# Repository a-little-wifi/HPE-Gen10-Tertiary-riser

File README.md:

# HPE DL360/DL380 Gen10 Tertiary riser reverse engineering

KiCad project of an almost-complete recreation of the 875539-001 riser for the DL360 Gen10 which plugs into the tertiary riser slot on the motherboard.  
My goal is to recreate the tertiary riser for the DL380 Gen10, which should use the same pinout.

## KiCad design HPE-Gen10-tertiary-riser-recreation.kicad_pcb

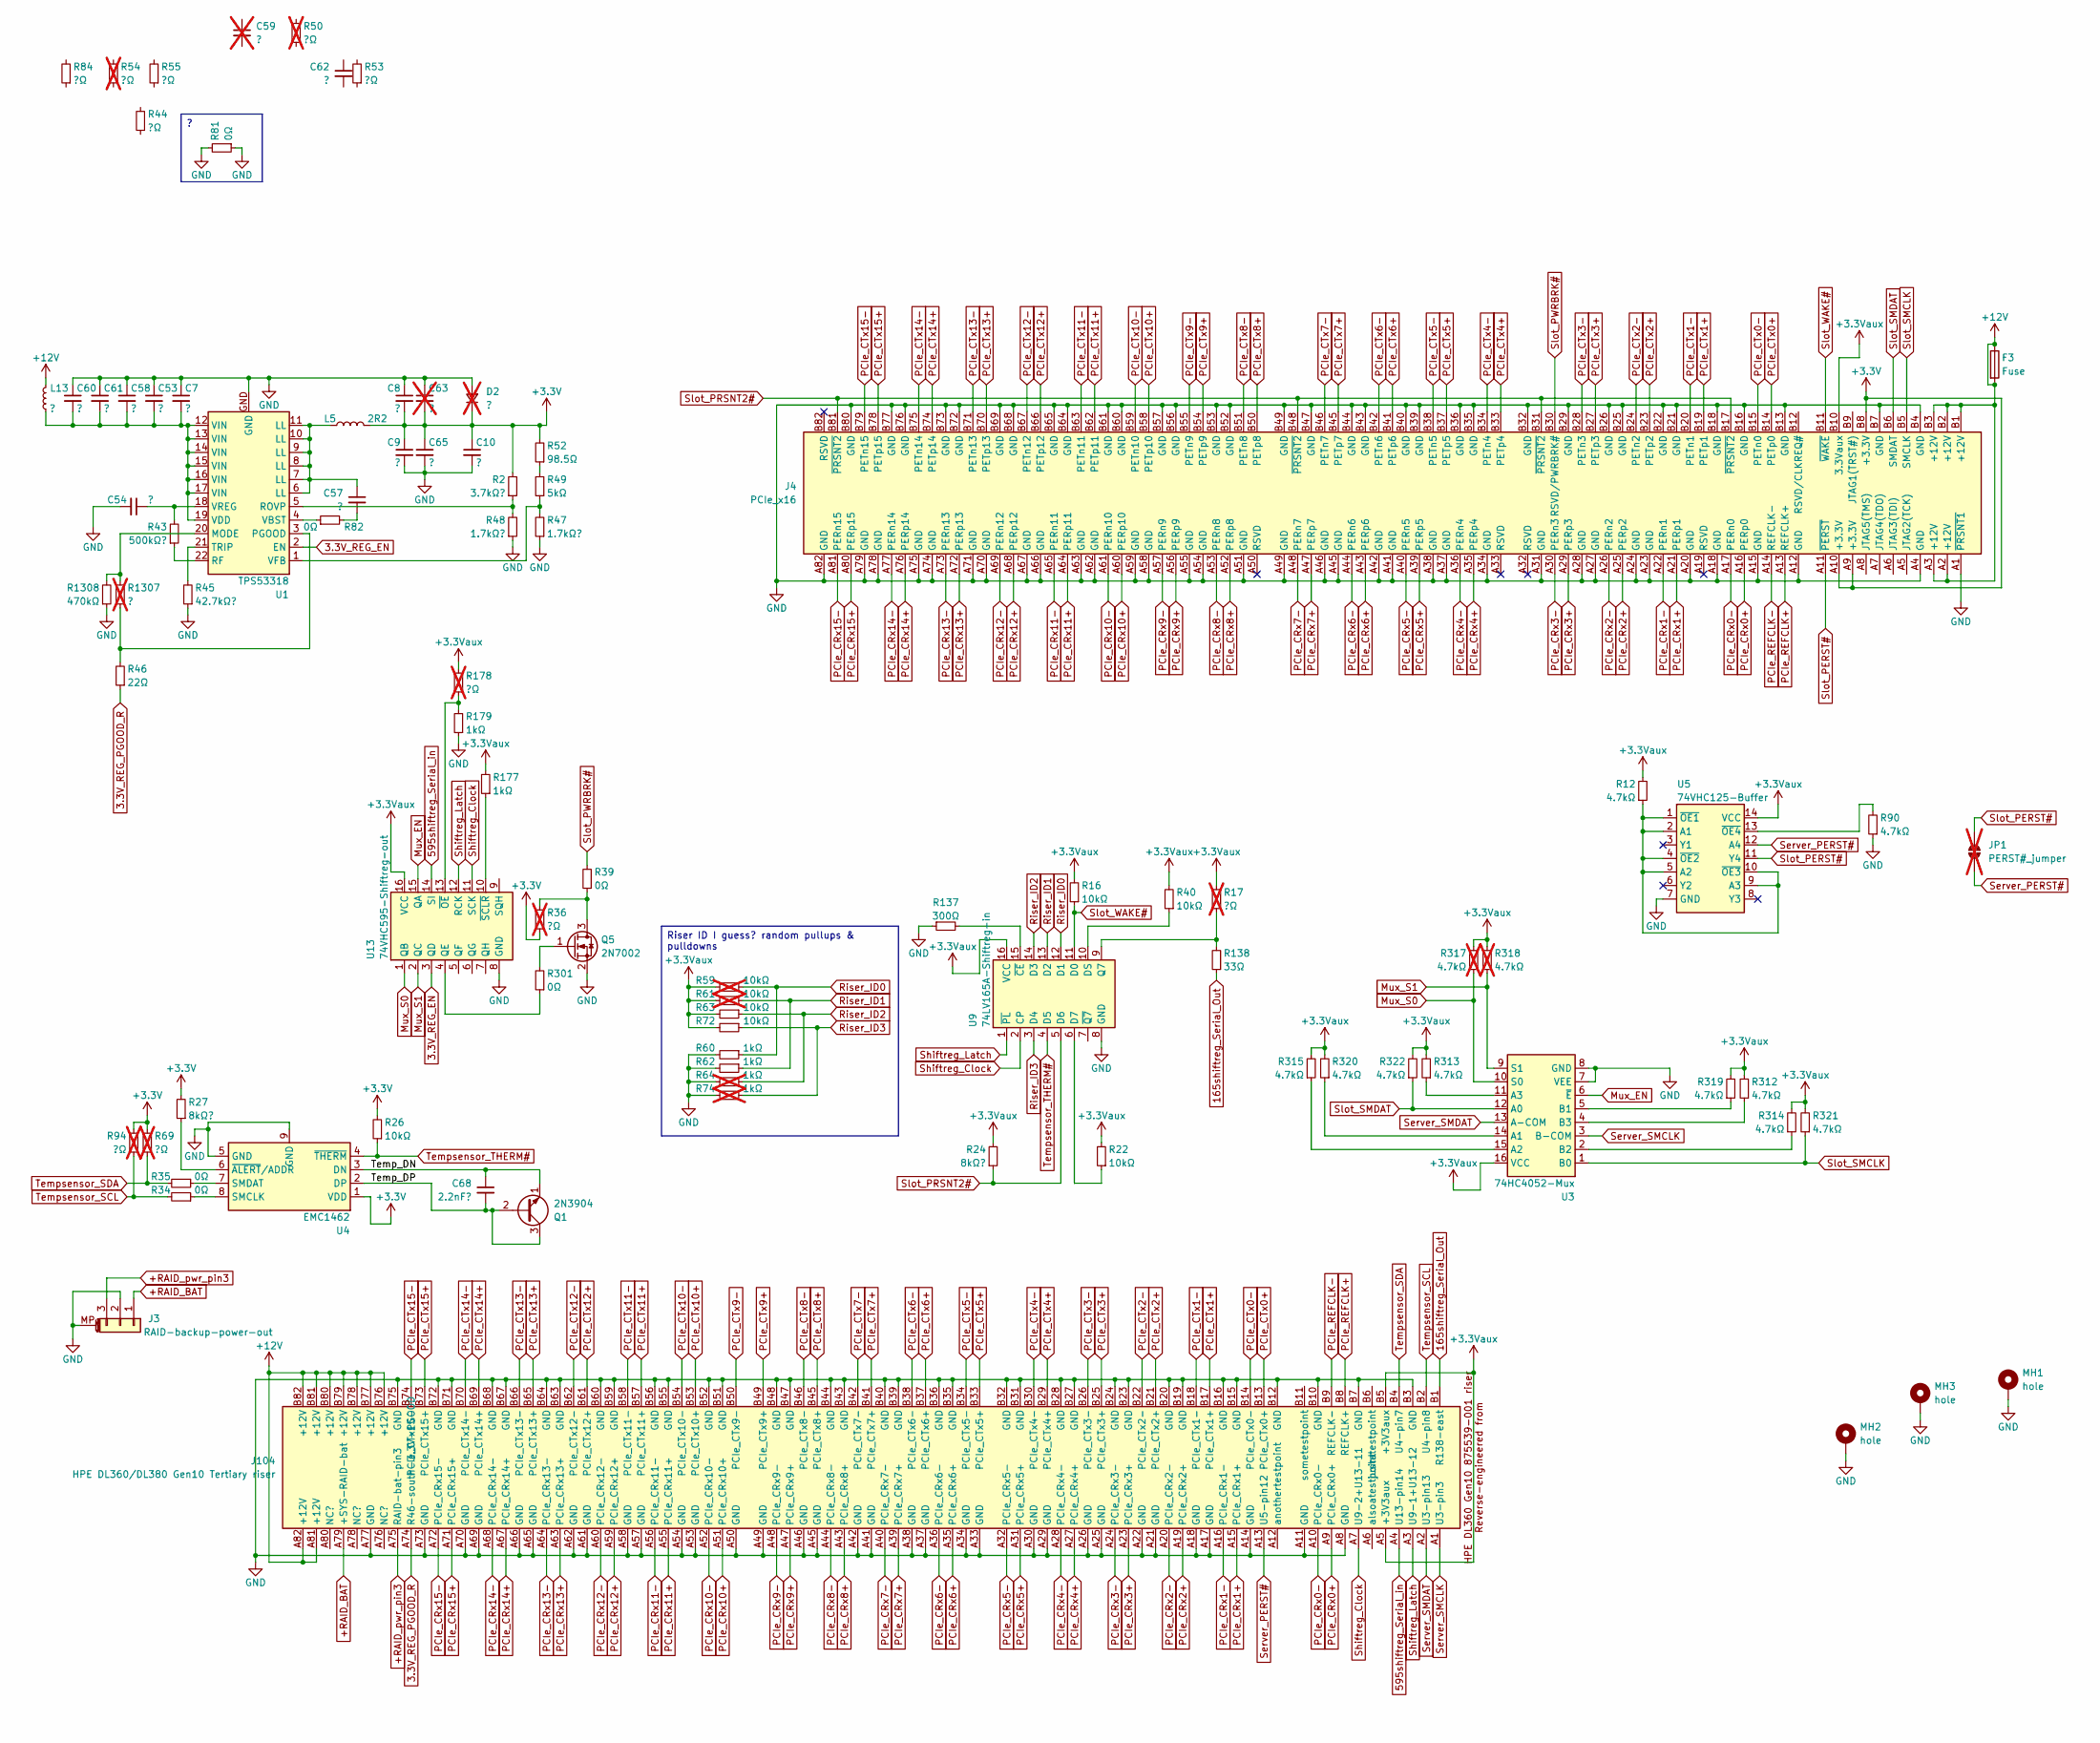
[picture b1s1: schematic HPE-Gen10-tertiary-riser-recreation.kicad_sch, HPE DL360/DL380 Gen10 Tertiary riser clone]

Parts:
C7, C10, C54, C57, C62: ?; C_0402_1005Metric
C8, C9, C65: ?; C_0805_2012Metric
C53: ?; C_0603_1608Metric
C58, C60, C61: ?; C_1206_3216Metric
C59: ?; C_0402_1005Metric; not fitted
C63: ?; C_0805_2012Metric; not fitted
C68: 2.2nF?; C_0402_1005Metric
D2: ?; D_1206_3216Metric; not fitted
F3: Fuse; Fuse_1206_3216Metric
J3: RAID-backup-power-out
J4: PCIe_x16; PCIe_x16_tht_smallholes
J104: HPE DL360/DL380 Gen10 Tertiary riser; BUS_PCIexpress_x16
JP1: PERST#_jumper; SolderJumper-2_P1.3mm_Open_TrianglePad1.0x1.5mm; not fitted
L5: 2R2; L_Sumida_CDMC6D28_7.25x6.5mm
L13: ?; L_1206_3216Metric
MH1, MH2, MH3: hole; MountingHole_2.5mm_Pad
Q1: 2N3904; TSOT-23
Q5: 2N7002; SOT-23
R2: 3.7kΩ?; R_0402_1005Metric
R12, R90, R312, R313, R314, R315, R319, R320, R321, R322: 4.7kΩ; R_0402_1005Metric
R16, R22, R26, R40, R63, R72: 10kΩ; R_0402_1005Metric
R17, R36, R50, R54, R69, R94, R178: ?Ω; R_0402_1005Metric; not fitted
R24, R27: 8kΩ?; R_0402_1005Metric
R34, R35, R39, R81, R82, R301: 0Ω; R_0402_1005Metric
R43: 500kΩ?; R_0402_1005Metric
R44, R53, R55, R84: ?Ω; R_0402_1005Metric
R45: 42.7kΩ?; R_0402_1005Metric
R46: 22Ω; R_0402_1005Metric
R47, R48: 1.7kΩ?; R_0402_1005Metric
R49: 5kΩ; R_0402_1005Metric
R52: 98.5Ω; R_0402_1005Metric
R59, R61: 10kΩ; R_0402_1005Metric; not fitted
R60, R62, R177, R179: 1kΩ; R_0402_1005Metric
R64, R74: 1kΩ; R_0402_1005Metric; not fitted
R137: 300Ω; R_0402_1005Metric
R138: 33Ω; R_0402_1005Metric
R317, R318: 4.7kΩ; R_0402_1005Metric; not fitted
R1307: ?; R_0402_1005Metric; not fitted
R1308: 470kΩ; R_0402_1005Metric
U1: TPS53318
U3: 74HC4052-Mux; TSSOP-16_4.4x5mm_P0.65mm
U4: EMC1462; DFN-8-1EP_3x2mm_P0.5mm_EP1.3x1.5mm
U5: 74VHC125-Buffer; TSSOP-14_4.4x5mm_P0.65mm
U9: 74LV165A-Shiftreg-in; SOIC-16_3.9x9.9mm_P1.27mm
U13: 74VHC595-Shiftreg-out; TSSOP-16_4.4x5mm_P0.65mm

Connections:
3.3V_REG_EN: U1.2 (EN), U13.3 (QD)
3.3V_REG_PGOOD_R: J104.A74 (R46-south-3.3V-PGOOD), R46.1
165shiftreg_Serial_Out: J104.B1 (R138-east), R138.1
595shiftreg_Serial_in: J104.A4 (U13-pin14), U13.14 (SI)
+3.3V: C8.2, C9.1, C10.1, C63.2, C65.1, D2.1 (K), J4.A9 (+3.3V), J4.A10 (+3.3V), J4.B8 (+3.3V), L5.2, R2.2, R26.2, R27.2, R36.1, R52.2, R69.2, R94.2, U4.1 (VDD)
+3.3Vaux: J4.B10 (3.3Vaux), J104.A5 (+3V3aux), J104.B5 (+3V3aux), R12.2, R16.2, R17.2, R22.2, R24.2, R40.2, R59.2, R61.2, R63.2, R72.2, R177.2, R178.2, R312.2, R313.2, R314.2, R315.2, R317.2, R318.2, R319.2, R320.2, R321.2, R322.2, U3.16 (VCC), U5.14 (VCC), U9.16 (VCC), U13.16 (VCC)
+12V: F3.1, F3.2, J4.A2 (+12V), J4.A3 (+12V), J4.B1 (+12V), J4.B2 (+12V), J4.B3 (+12V), J104.A81 (+12V), J104.A82 (+12V), J104.B76 (+12V), J104.B77 (+12V), J104.B78 (+12V), J104.B79 (+12V), J104.B80 (+12V), J104.B81 (+12V), J104.B82 (+12V), L13.2
+RAID_BAT: J3.1, J104.A79 (+SYS-RAID-bat)
+RAID_pwr_pin3: J3.3, J104.A75 (RAID-bat-pin3)
/Temp_DN: C68.1, Q1.1 (E), U4.3 (DN)
/Temp_DP: C68.2, Q1.2 (B), Q1.3 (C), U4.2 (DP)
GND: C7.1, C8.1, C9.2, C10.2, C53.1, C54.2, C58.1, C60.1, C61.1, C63.1, C65.2, D2.2 (A), J3.2, J3.MP (MountPin), J4.A1 (~PRSNT1), J4.A4 (GND), J4.A12 (GND), J4.A15 (GND), J4.A18 (GND), J4.A20 (GND), J4.A23 (GND), J4.A24 (GND), J4.A27 (GND), J4.A28 (GND), J4.A31 (GND), J4.A34 (GND), J4.A37 (GND), J4.A38 (GND), J4.A41 (GND), J4.A42 (GND), J4.A45 (GND), J4.A46 (GND), J4.A49 (GND), J4.A51 (GND), J4.A54 (GND), J4.A55 (GND), J4.A58 (GND), J4.A59 (GND), J4.A62 (GND), J4.A63 (GND), J4.A66 (GND), J4.A67 (GND), J4.A70 (GND), J4.A71 (GND), J4.A74 (GND), J4.A75 (GND), J4.A78 (GND), J4.A79 (GND), J4.A82 (GND), J4.B4 (GND), J4.B7 (GND), J4.B13 (GND), J4.B16 (GND), J4.B18 (GND), J4.B21 (GND), J4.B22 (GND), J4.B25 (GND), J4.B26 (GND), J4.B29 (GND), J4.B32 (GND), J4.B35 (GND), J4.B36 (GND), J4.B39 (GND), J4.B40 (GND), J4.B43 (GND), J4.B44 (GND), J4.B47 (GND), J4.B49 (GND), J4.B52 (GND), J4.B53 (GND), J4.B56 (GND), J4.B57 (GND), J4.B60 (GND), J4.B61 (GND), J4.B64 (GND), J4.B65 (GND), J4.B68 (GND), J4.B69 (GND), J4.B72 (GND), J4.B73 (GND), J4.B76 (GND), J4.B77 (GND), J4.B80 (GND), J104.A8 (GND), J104.A11 (GND), J104.A14 (GND), J104.A17 (GND), J104.A18 (GND), J104.A21 (GND), J104.A22 (GND), J104.A25 (GND), J104.A26 (GND), J104.A29 (GND), J104.A30 (GND), J104.A33 (GND), J104.A34 (GND), J104.A37 (GND), J104.A38 (GND), J104.A41 (GND), J104.A42 (GND), J104.A45 (GND), J104.A46 (GND), J104.A49 (GND), J104.A50 (GND), J104.A53 (GND), J104.A54 (GND), J104.A57 (GND), J104.A58 (GND), J104.A61 (GND), J104.A62 (GND), J104.A65 (GND), J104.A66 (GND), J104.A69 (GND), J104.A70 (GND), J104.A73 (GND), J104.A77 (GND), J104.B3 (GND), J104.B7 (GND), J104.B10 (GND), J104.B12 (GND), J104.B15 (GND), J104.B16 (GND), J104.B19 (GND), J104.B20 (GND), J104.B23 (GND), J104.B24 (GND), J104.B27 (GND), J104.B28 (GND), J104.B31 (GND), J104.B32 (GND), J104.B35 (GND), J104.B36 (GND), J104.B39 (GND), J104.B40 (GND), J104.B43 (GND), J104.B44 (GND), J104.B47 (GND), J104.B48 (GND), J104.B51 (GND), J104.B52 (GND), J104.B55 (GND), J104.B56 (GND), J104.B59 (GND), J104.B60 (GND), J104.B63 (GND), J104.B64 (GND), J104.B67 (GND), J104.B68 (GND), J104.B71 (GND), J104.B72 (GND), J104.B75 (GND), MH1.1, MH2.1, MH3.1, Q5.2 (S), R45.1, R47.1, R48.1, R60.2, R62.2, R64.2, R74.2, R81.1, R81.2, R90.1, R137.1, R179.1, R1308.1, U1.GND, U3.7 (VEE), U3.8 (GND), U4.5 (GND), U4.9 (GND), U5.7 (GND), U9.8 (GND), U13.8 (GND)
Mux_EN: U3.6 (~E), U13.15 (QA)
Mux_S0: R317.1, U3.10 (S0), U13.1 (QB)
Mux_S1: R318.1, U3.9 (S1), U13.2 (QC)
unnamed: C57.1, L5.1, U1.6 (LL), U1.7 (LL), U1.8 (LL), U1.9 (LL), U1.10 (LL), U1.11 (LL)
unnamed: C57.2, R82.2
unnamed: Q5.3 (D), R36.2, R39.1
unnamed: Q5.1 (G), R301.2
unnamed: R49.2, R52.1
unnamed: R1307.2, R1308.2, U1.20 (MODE)
unnamed: R46.2, R1307.1, U1.3 (PGOOD)
unnamed: R43.1, U1.22 (RF)
unnamed: R2.1, R48.2, U1.5 (ROVP)
unnamed: R45.2, U1.21 (TRIP)
unnamed: R82.1, U1.4 (VBST)
unnamed: C7.2, C53.2, C58.2, C60.2, C61.2, L13.1, U1.12 (VIN), U1.13 (VIN), U1.14 (VIN), U1.15 (VIN), U1.16 (VIN), U1.17 (VIN), U1.19 (VDD)
unnamed: R47.2, R49.1, U1.1 (VFB)
unnamed: C54.1, R43.2, U1.18 (VREG)
unnamed: R320.1, U3.14 (A1)
unnamed: R315.1, U3.15 (A2)
unnamed: R313.1, U3.11 (A3)
unnamed: R319.1, U3.5 (B1)
unnamed: R314.1, U3.2 (B2)
unnamed: R312.1, U3.4 (B3)
unnamed: R34.1, U4.8 (SMCLK)
unnamed: R35.1, U4.7 (SMDAT)
unnamed: R27.1, U4.6 (~ALERT/ADDR)
unnamed: R12.1, U5.1 (~OE1), U5.2 (A1), U5.4 (~OE2), U5.5 (A2), U5.9 (A3), U5.10 (~OE3)
unnamed: R90.2, U5.13 (~OE4)
unnamed: R22.1, U9.6 (D7)
unnamed: R40.1, U9.10 (DS)
unnamed: R17.1, R138.2, U9.9 (Q7)
unnamed: R137.2, U9.15 (~CE)
unnamed: R301.1, U13.4 (QE)
unnamed: R178.1, R179.2, U13.13 (~OE)
unnamed: R177.1, U13.10 (~SCLR)
PCIe_CRx0+: J4.A16 (PERp0), J104.A9 (PCIe_CRx0+)
PCIe_CRx0-: J4.A17 (PERn0), J104.A10 (PCIe_CRx0-)
PCIe_CRx1+: J4.A21 (PERp1), J104.A15 (PCIe_CRx1+)
PCIe_CRx1-: J4.A22 (PERn1), J104.A16 (PCIe_CRx1-)
PCIe_CRx2+: J4.A25 (PERp2), J104.A19 (PCIe_CRx2+)
PCIe_CRx2-: J4.A26 (PERn2), J104.A20 (PCIe_CRx2-)
PCIe_CRx3+: J4.A29 (PERp3), J104.A23 (PCIe_CRx3+)
PCIe_CRx3-: J4.A30 (PERn3), J104.A24 (PCIe_CRx3-)
PCIe_CRx4+: J4.A35 (PERp4), J104.A27 (PCIe_CRx4+)
PCIe_CRx4-: J4.A36 (PERn4), J104.A28 (PCIe_CRx4-)
PCIe_CRx5+: J4.A39 (PERp5), J104.A31 (PCIe_CRx5+)
PCIe_CRx5-: J4.A40 (PERn5), J104.A32 (PCIe_CRx5-)
PCIe_CRx6+: J4.A43 (PERp6), J104.A35 (PCIe_CRx6+)
PCIe_CRx6-: J4.A44 (PERn6), J104.A36 (PCIe_CRx6-)
PCIe_CRx7+: J4.A47 (PERp7), J104.A39 (PCIe_CRx7+)
PCIe_CRx7-: J4.A48 (PERn7), J104.A40 (PCIe_CRx7-)
PCIe_CRx8+: J4.A52 (PERp8), J104.A43 (PCIe_CRx8+)
PCIe_CRx8-: J4.A53 (PERn8), J104.A44 (PCIe_CRx8-)
PCIe_CRx9+: J4.A56 (PERp9), J104.A47 (PCIe_CRx9+)
PCIe_CRx9-: J4.A57 (PERn9), J104.A48 (PCIe_CRx9-)
PCIe_CRx10+: J4.A60 (PERp10), J104.A51 (PCIe_CRx10+)
PCIe_CRx10-: J4.A61 (PERn10), J104.A52 (PCIe_CRx10-)
PCIe_CRx11+: J4.A64 (PERp11), J104.A55 (PCIe_CRx11+)
PCIe_CRx11-: J4.A65 (PERn11), J104.A56 (PCIe_CRx11-)
PCIe_CRx12+: J4.A68 (PERp12), J104.A59 (PCIe_CRx12+)
PCIe_CRx12-: J4.A69 (PERn12), J104.A60 (PCIe_CRx12-)
PCIe_CRx13+: J4.A72 (PERp13), J104.A63 (PCIe_CRx13+)
PCIe_CRx13-: J4.A73 (PERn13), J104.A64 (PCIe_CRx13-)
PCIe_CRx14+: J4.A76 (PERp14), J104.A67 (PCIe_CRx14+)
PCIe_CRx14-: J4.A77 (PERn14), J104.A68 (PCIe_CRx14-)
PCIe_CRx15+: J4.A80 (PERp15), J104.A71 (PCIe_CRx15+)
PCIe_CRx15-: J4.A81 (PERn15), J104.A72 (PCIe_CRx15-)
PCIe_CTx0+: J4.B14 (PETp0), J104.B13 (PCIe_CTx0+)
PCIe_CTx0-: J4.B15 (PETn0), J104.B14 (PCIe_CTx0-)
PCIe_CTx1+: J4.B19 (PETp1), J104.B17 (PCIe_CTx1+)
PCIe_CTx1-: J4.B20 (PETn1), J104.B18 (PCIe_CTx1-)
PCIe_CTx2+: J4.B23 (PETp2), J104.B21 (PCIe_CTx2+)
PCIe_CTx2-: J4.B24 (PETn2), J104.B22 (PCIe_CTx2-)
PCIe_CTx3+: J4.B27 (PETp3), J104.B25 (PCIe_CTx3+)
PCIe_CTx3-: J4.B28 (PETn3), J104.B26 (PCIe_CTx3-)
PCIe_CTx4+: J4.B33 (PETp4), J104.B29 (PCIe_CTx4+)
PCIe_CTx4-: J4.B34 (PETn4), J104.B30 (PCIe_CTx4-)
PCIe_CTx5+: J4.B37 (PETp5), J104.B33 (PCIe_CTx5+)
PCIe_CTx5-: J4.B38 (PETn5), J104.B34 (PCIe_CTx5-)
PCIe_CTx6+: J4.B41 (PETp6), J104.B37 (PCIe_CTx6+)
PCIe_CTx6-: J4.B42 (PETn6), J104.B38 (PCIe_CTx6-)
PCIe_CTx7+: J4.B45 (PETp7), J104.B41 (PCIe_CTx7+)
PCIe_CTx7-: J4.B46 (PETn7), J104.B42 (PCIe_CTx7-)
PCIe_CTx8+: J4.B50 (PETp8), J104.B45 (PCIe_CTx8+)
PCIe_CTx8-: J4.B51 (PETn8), J104.B46 (PCIe_CTx8-)
PCIe_CTx9+: J4.B54 (PETp9), J104.B49 (PCIe_CTx9+)
PCIe_CTx9-: J4.B55 (PETn9), J104.B50 (PCIe_CTx9-)
PCIe_CTx10+: J4.B58 (PETp10), J104.B53 (PCIe_CTx10+)
PCIe_CTx10-: J4.B59 (PETn10), J104.B54 (PCIe_CTx10-)
PCIe_CTx11+: J4.B62 (PETp11), J104.B57 (PCIe_CTx11+)
PCIe_CTx11-: J4.B63 (PETn11), J104.B58 (PCIe_CTx11-)
PCIe_CTx12+: J4.B66 (PETp12), J104.B61 (PCIe_CTx12+)
PCIe_CTx12-: J4.B67 (PETn12), J104.B62 (PCIe_CTx12-)
PCIe_CTx13+: J4.B70 (PETp13), J104.B65 (PCIe_CTx13+)
PCIe_CTx13-: J4.B71 (PETn13), J104.B66 (PCIe_CTx13-)
PCIe_CTx14+: J4.B74 (PETp14), J104.B69 (PCIe_CTx14+)
PCIe_CTx14-: J4.B75 (PETn14), J104.B70 (PCIe_CTx14-)
PCIe_CTx15+: J4.B78 (PETp15), J104.B73 (PCIe_CTx15+)
PCIe_CTx15-: J4.B79 (PETn15), J104.B74 (PCIe_CTx15-)
PCIe_REFCLK+: J4.A13 (REFCLK+), J104.B8 (REFCLK+)
PCIe_REFCLK-: J4.A14 (REFCLK-), J104.B9 (REFCLK-)
Riser_ID0: R59.1, R60.1, U9.12 (D1)
Riser_ID1: R61.1, R62.1, U9.13 (D2)
Riser_ID2: R63.1, R64.1, U9.14 (D3)
Riser_ID3: R72.1, R74.1, U9.3 (D4)
Server_PERST#: J104.A13 (U5-pin12), JP1.1 (A), U5.12 (A4)
Server_SMCLK: J104.A1 (U3-pin3), U3.3 (B-COM)
Server_SMDAT: J104.A2 (U3-pin13), U3.13 (A-COM)
Shiftreg_Clock: J104.A7 (U9-2+U13-11), U9.2 (CP), U13.11 (SCK)
Shiftreg_Latch: J104.A3 (U9-1+U13-12), U9.1 (~PL), U13.12 (RCK)
Slot_PERST#: J4.A11 (~PERST), JP1.2 (B), U5.11 (Y4)
Slot_PRSNT2#: J4.B17 (~PRSNT2), J4.B31 (~PRSNT2), J4.B48 (~PRSNT2), J4.B81 (~PRSNT2), R24.1, U9.5 (D6)
Slot_PWRBRK#: J4.B30 (RSVD/PWRBRK#), R39.2
Slot_SMCLK: J4.B5 (SMCLK), R321.1, U3.1 (B0)
Slot_SMDAT: J4.B6 (SMDAT), R322.1, U3.12 (A0)
Slot_WAKE#: J4.B11 (~WAKE), R16.1, U9.11 (D0)
Tempsensor_SCL: J104.B2 (U4-pin8), R34.2, R94.1
Tempsensor_SDA: J104.B4 (U4-pin7), R35.2, R69.1
Tempsensor_THERM#: R26.1, U4.4 (~THERM), U9.4 (D5)

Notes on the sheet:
Riser ID I guess? random pullups & pulldowns

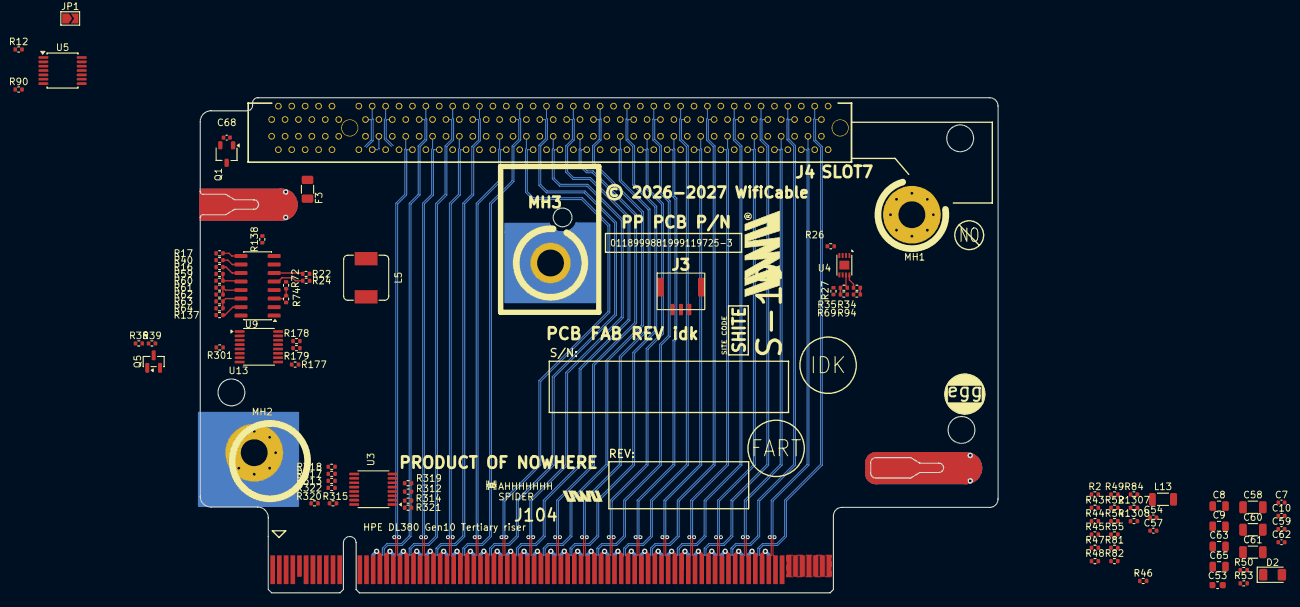
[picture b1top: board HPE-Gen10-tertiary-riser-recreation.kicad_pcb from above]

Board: 4 copper layers, 119.0 x 73.9 mm, 90 parts (0 on the bottom side), 127 nets.

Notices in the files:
HPE-Gen10-tertiary-riser-recreation.kicad_pcb:
© 2026-2027 WifiCable
